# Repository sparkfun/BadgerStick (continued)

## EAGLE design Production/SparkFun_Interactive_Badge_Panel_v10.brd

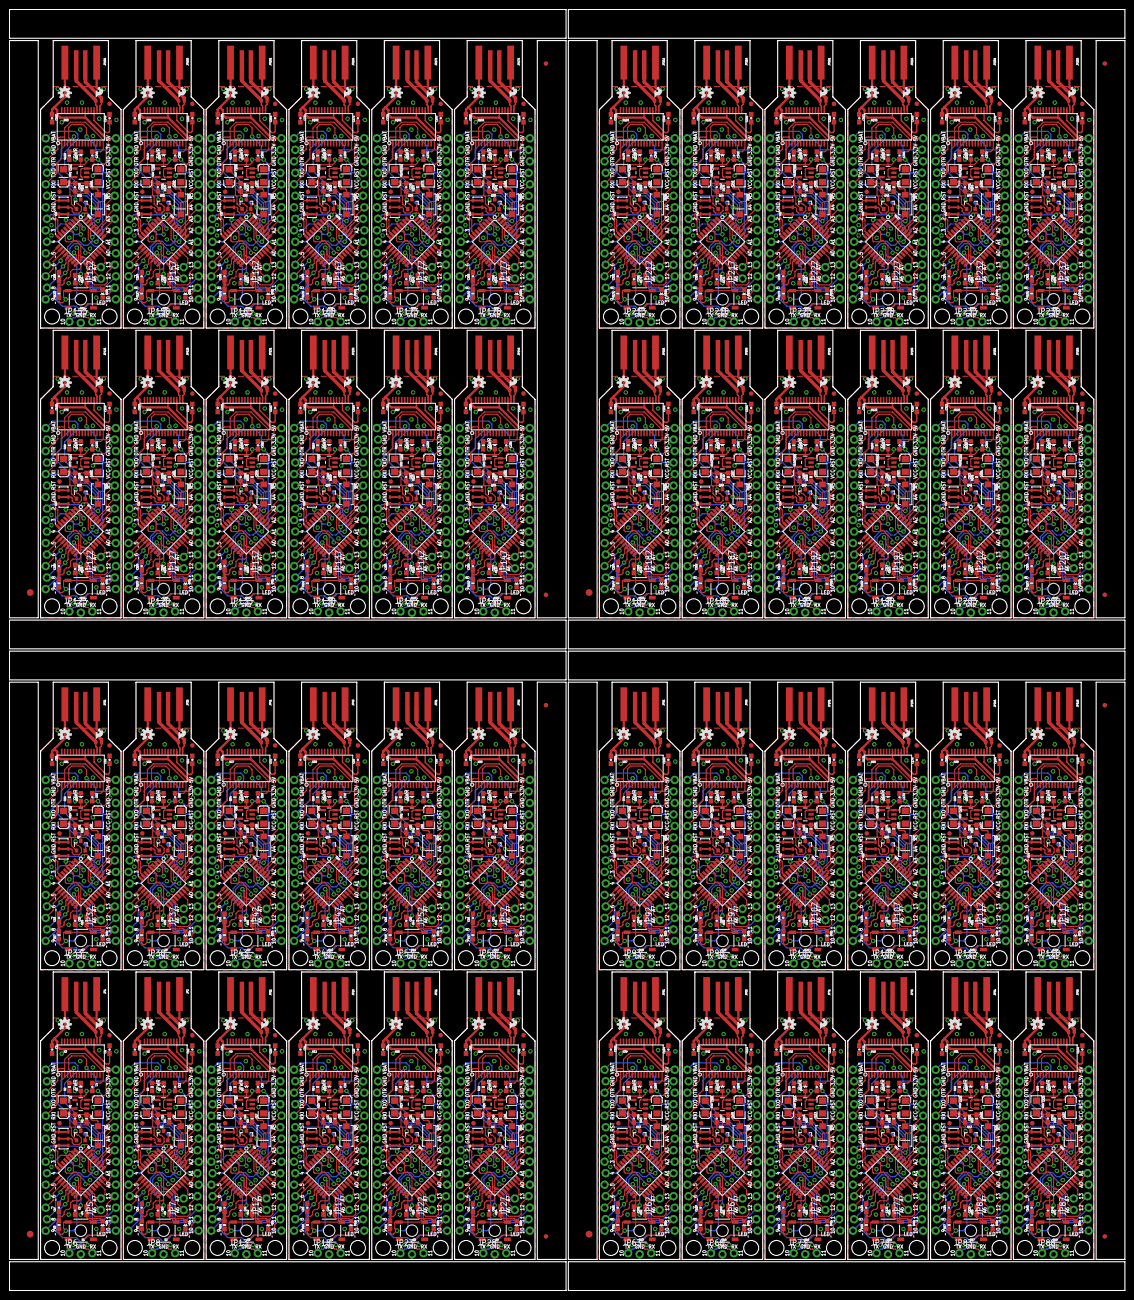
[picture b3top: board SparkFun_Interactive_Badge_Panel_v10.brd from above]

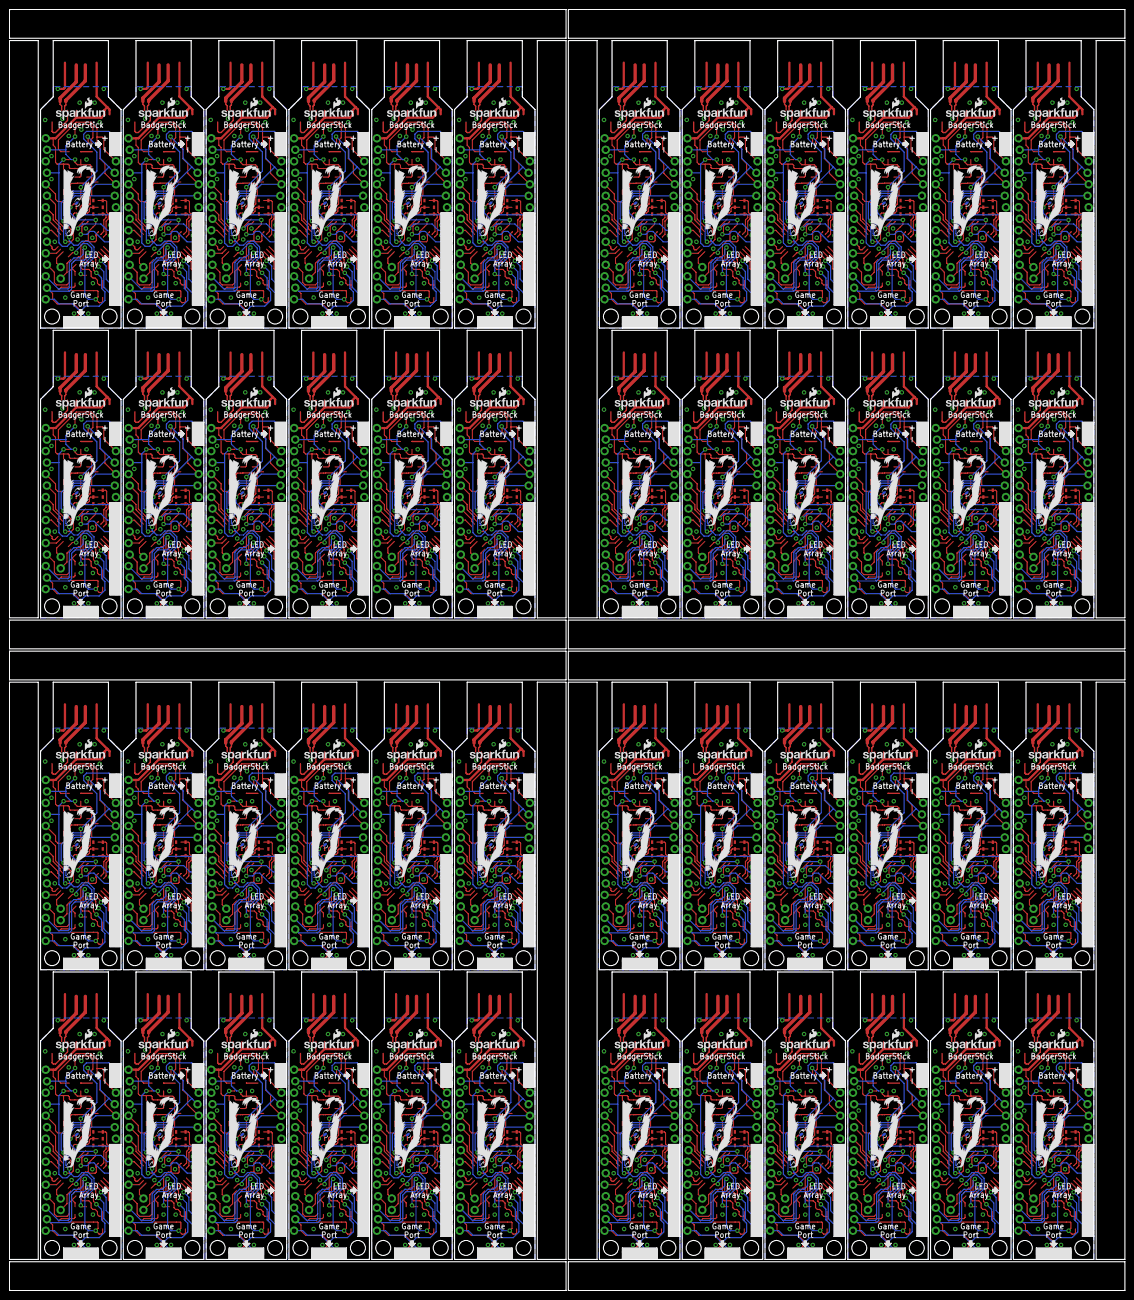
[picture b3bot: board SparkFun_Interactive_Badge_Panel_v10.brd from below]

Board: 2 copper layers, 246.4 x 283.0 mm, 1644 parts (96 on the bottom side), 1776 nets.

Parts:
C1, C2, C9, C10, C17, C18, C25, C26, C33, C34, C41, C42, C49, C50, C57, C58, C65, C66, C73, C74, C81, C82, C89, C90, C97, C98, C105, C106, C113, C114, C121, C122, C129, C130, C137, C138, C145, C146, C153, C154, C161, C162, C169, C170, C177, C178, C185, C186, C193, C194, C201, C202, C209, C210, C217, C218, C225, C226, C233, C234, C241, C242, C249, C250, C257, C258, C265, C266, C273, C274, C281, C282, C289, C290, C297, C298, C305, C306, C313, C314, C321, C322, C329, C330, C337, C338, C345, C346, C353, C354, C361, C362, C369, C370, C377, C378: 10uF; EIA3216
C3, C4, C5, C6, C7, C8, C11, C12, C13, C14, C15, C16, C19, C20, C21, C22, C23, C24, C27, C28, C29, C30, C31, C32, C35, C36, C37, C38, C39, C40, C43, C44, C45, C46, C47, C48, C51, C52, C53, C54, C55, C56, C59, C60, C61, C62, C63, C64, C67, C68, C69, C70, C71, C72, C75, C76, C77, C78, C79, C80, C83, C84, C85, C86, C87, C88, C91, C92, C93, C94, C95, C96, C99, C100, C101, C102, C103, C104, C107, C108, C109, C110, C111, C112, C115, C116, C117, C118, C119, C120, C123, C124, C125, C126, C127, C128, C131, C132, C133, C134, C135, C136, C139, C140, C141, C142, C143, C144, C147, C148, C149, C150, C151, C152, C155, C156, C157, C158, C159, C160, C163, C164, C165, C166, C167, C168, C171, C172, C173, C174, C175, C176, C179, C180, C181, C182, C183, C184, C187, C188, C189, C190, C191, C192, C195, C196, C197, C198, C199, C200, C203, C204, C205, C206, C207, C208, C211, C212, C213, C214, C215, C216, C219, C220, C221, C222, C223, C224, C227, C228, C229, C230, C231, C232, C235, C236, C237, C238, C239, C240, C243, C244, C245, C246, C247, C248, C251, C252, C253, C254, C255, C256, C259, C260, C261, C262, C263, C264, C267, C268, C269, C270, C271, C272, C275, C276, C277, C278, C279, C280, C283, C284, C285, C286, C287, C288, C291, C292, C293, C294, C295, C296, C299, C300, C301, C302, C303, C304, C307, C308, C309, C310, C311, C312, C315, C316, C317, C318, C319, C320, C323, C324, C325, C326, C327, C328, C331, C332, C333, C334, C335, C336, C339, C340, C341, C342, C343, C344, C347, C348, C349, C350, C351, C352, C355, C356, C357, C358, C359, C360, C363, C364, C365, C366, C367, C368, C371, C372, C373, C374, C375, C376, C379, C380, C381, C382, C383, C384: 0.1uF; 0603-CAP
D1, D4, D7, D10, D13, D16, D19, D22, D25, D28, D31, D34, D37, D40, D43, D46, D49, D52, D55, D58, D61, D64, D67, D70, D73, D76, D79, D82, D85, D88, D91, D94, D97, D100, D103, D106, D109, D112, D115, D118, D121, D124, D127, D130, D133, D136, D139, D142: MBRA140; SMA-DIODE
D2, D5, D8, D11, D14, D17, D20, D23, D26, D29, D32, D35, D38, D41, D44, D47, D50, D53, D56, D59, D62, D65, D68, D71, D74, D77, D80, D83, D86, D89, D92, D95, D98, D101, D104, D107, D110, D113, D116, D119, D122, D125, D128, D131, D134, D137, D140, D143: RED; LED-0603
D3, D6, D9, D12, D15, D18, D21, D24, D27, D30, D33, D36, D39, D42, D45, D48, D51, D54, D57, D60, D63, D66, D69, D72, D75, D78, D81, D84, D87, D90, D93, D96, D99, D102, D105, D108, D111, D114, D117, D120, D123, D126, D129, D132, D135, D138, D141, D144: GREEN; LED-0603
E$1, E$6, E$9, E$12: FIDUCIAL-1.5X3
E$2, E$3, E$4, E$5, E$7, E$8, E$10, E$11: FIDUCIAL-1X2
FID1, FID2, FID3, FID4, FID5, FID6, FID7, FID8, FID9, FID10, FID11, FID12, FID13, FID14, FID15, FID16, FID17, FID18, FID19, FID20, FID21, FID22, FID23, FID24, FID25, FID26, FID27, FID28, FID29, FID30, FID31, FID32, FID33, FID34, FID35, FID36, FID37, FID38, FID39, FID40, FID41, FID42, FID43, FID44, FID45, FID46, FID47, FID48, FID49, FID50, FID51, FID52, FID53, FID54, FID55, FID56, FID57, FID58, FID59, FID60, FID61, FID62, FID63, FID64, FID65, FID66, FID67, FID68, FID69, FID70, FID71, FID72, FID73, FID74, FID75, FID76, FID77, FID78, FID79, FID80, FID81, FID82, FID83, FID84, FID85, FID86, FID87, FID88, FID89, FID90, FID91, FID92, FID93, FID94, FID95, FID96: FIDUCIAL1X2; FIDUCIAL-1X2
JP1, JP2, JP11, JP16, JP21, JP26, JP31, JP36, JP41, JP46, JP51, JP56, JP61, JP66, JP71, JP76, JP81, JP86, JP91, JP96, JP101, JP106, JP111, JP116, JP121, JP126, JP131, JP136, JP141, JP146, JP151, JP156, JP161, JP166, JP171, JP176, JP181, JP186, JP191, JP196, JP201, JP206, JP211, JP216, JP221, JP226, JP231, JP236: USBPCB; USB-A-PCB
JP3, JP4, JP9, JP10, JP14, JP15, JP19, JP20, JP24, JP25, JP29, JP30, JP34, JP35, JP39, JP40, JP44, JP45, JP49, JP50, JP54, JP55, JP59, JP60, JP64, JP65, JP69, JP70, JP74, JP75, JP79, JP80, JP84, JP85, JP89, JP90, JP94, JP95, JP99, JP100, JP104, JP105, JP109, JP110, JP114, JP115, JP119, JP120, JP124, JP125, JP129, JP130, JP134, JP135, JP139, JP140, JP144, JP145, JP149, JP150, JP154, JP155, JP159, JP160, JP164, JP165, JP169, JP170, JP174, JP175, JP179, JP180, JP184, JP185, JP189, JP190, JP194, JP195, JP199, JP200, JP204, JP205, JP209, JP210, JP214, JP215, JP219, JP220, JP224, JP225, JP229, JP230, JP234, JP235, JP239, JP240: M15LOCK_NO_SILK; 1X15_LOCK_NO_SILK
JP5, JP7, JP12, JP17, JP22, JP27, JP32, JP37, JP42, JP47, JP52, JP57, JP62, JP67, JP72, JP77, JP82, JP87, JP92, JP97, JP102, JP107, JP112, JP117, JP122, JP127, JP132, JP137, JP142, JP147, JP152, JP157, JP162, JP167, JP172, JP177, JP182, JP187, JP192, JP197, JP202, JP207, JP212, JP217, JP222, JP227, JP232, JP237: M021X02_NO_SILK; 1X02_NO_SILK
JP6, JP8, JP13, JP18, JP23, JP28, JP33, JP38, JP43, JP48, JP53, JP58, JP63, JP68, JP73, JP78, JP83, JP88, JP93, JP98, JP103, JP108, JP113, JP118, JP123, JP128, JP133, JP138, JP143, JP148, JP153, JP158, JP163, JP168, JP173, JP178, JP183, JP188, JP193, JP198, JP203, JP208, JP213, JP218, JP223, JP228, JP233, JP238: M03LOCK Female; 1X03_LOCK_NO_SILK
LOGO1, LOGO3, LOGO5, LOGO7, LOGO9, LOGO11, LOGO13, LOGO15, LOGO17, LOGO19, LOGO21, LOGO23, LOGO25, LOGO27, LOGO29, LOGO31, LOGO33, LOGO35, LOGO37, LOGO39, LOGO41, LOGO43, LOGO45, LOGO47, LOGO49, LOGO51, LOGO53, LOGO55, LOGO57, LOGO59, LOGO61, LOGO63, LOGO65, LOGO67, LOGO69, LOGO71, LOGO73, LOGO75, LOGO77, LOGO79, LOGO81, LOGO83, LOGO85, LOGO87, LOGO89, LOGO91, LOGO93, LOGO95: SFE_LOGO_FLAME.1_INCH; SFE_LOGO_FLAME_.1
LOGO2, LOGO4, LOGO6, LOGO8, LOGO10, LOGO12, LOGO14, LOGO16, LOGO18, LOGO20, LOGO22, LOGO24, LOGO26, LOGO28, LOGO30, LOGO32, LOGO34, LOGO36, LOGO38, LOGO40, LOGO42, LOGO44, LOGO46, LOGO48, LOGO50, LOGO52, LOGO54, LOGO56, LOGO58, LOGO60, LOGO62, LOGO64, LOGO66, LOGO68, LOGO70, LOGO72, LOGO74, LOGO76, LOGO78, LOGO80, LOGO82, LOGO84, LOGO86, LOGO88, LOGO90, LOGO92, LOGO94, LOGO96: OSHW-LOGOS; OSHW-LOGO-S
Q1, Q2, Q3, Q4, Q5, Q6, Q7, Q8, Q9, Q10, Q11, Q12, Q13, Q14, Q15, Q16, Q17, Q18, Q19, Q20, Q21, Q22, Q23, Q24, Q25, Q26, Q27, Q28, Q29, Q30, Q31, Q32, Q33, Q34, Q35, Q36, Q37, Q38, Q39, Q40, Q41, Q42, Q43, Q44, Q45, Q46, Q47, Q48: DMG2307L; SOT23-3
R1, R5, R9, R13, R17, R21, R25, R29, R33, R37, R41, R45, R49, R53, R57, R61, R65, R69, R73, R77, R81, R85, R89, R93, R97, R101, R105, R109, R113, R117, R121, R125, R129, R133, R137, R141, R145, R149, R153, R157, R161, R165, R169, R173, R177, R181, R185, R189: 100k; 0603-RES
R2, R3, R6, R7, R10, R11, R14, R15, R18, R19, R22, R23, R26, R27, R30, R31, R34, R35, R38, R39, R42, R43, R46, R47, R50, R51, R54, R55, R58, R59, R62, R63, R66, R67, R70, R71, R74, R75, R78, R79, R82, R83, R86, R87, R90, R91, R94, R95, R98, R99, R102, R103, R106, R107, R110, R111, R114, R115, R118, R119, R122, R123, R126, R127, R130, R131, R134, R135, R138, R139, R142, R143, R146, R147, R150, R151, R154, R155, R158, R159, R162, R163, R166, R167, R170, R171, R174, R175, R178, R179, R182, R183, R186, R187, R190, R191: 10K; 0603-RES
R4, R8, R12, R16, R20, R24, R28, R32, R36, R40, R44, R48, R52, R56, R60, R64, R68, R72, R76, R80, R84, R88, R92, R96, R100, R104, R108, R112, R116, R120, R124, R128, R132, R136, R140, R144, R148, R152, R156, R160, R164, R168, R172, R176, R180, R184, R188, R192: 330; 0603-RES
S1, S2, S3, S4, S5, S6, S7, S8, S9, S10, S11, S12, S13, S14, S15, S16, S17, S18, S19, S20, S21, S22, S23, S24, S25, S26, S27, S28, S29, S30, S31, S32, S33, S34, S35, S36, S37, S38, S39, S40, S41, S42, S43, S44, S45, S46, S47, S48: SWITCH-MOMENTARY-2SMD-REDUNDANT; TACTILE-SWITCH-SMD
STANDOFF1, STANDOFF2, STANDOFF3, STANDOFF4, STANDOFF5, STANDOFF6, STANDOFF7, STANDOFF8, STANDOFF9, STANDOFF10, STANDOFF11, STANDOFF12, STANDOFF13, STANDOFF14, STANDOFF15, STANDOFF16, STANDOFF17, STANDOFF18, STANDOFF19, STANDOFF20, STANDOFF21, STANDOFF22, STANDOFF23, STANDOFF24, STANDOFF25, STANDOFF26, STANDOFF27, STANDOFF28, STANDOFF29, STANDOFF30, STANDOFF31, STANDOFF32, STANDOFF33, STANDOFF34, STANDOFF35, STANDOFF36, STANDOFF37, STANDOFF38, STANDOFF39, STANDOFF40, STANDOFF41, STANDOFF42, STANDOFF43, STANDOFF44, STANDOFF45, STANDOFF46, STANDOFF47, STANDOFF48, STANDOFF49, STANDOFF50, STANDOFF51, STANDOFF52, STANDOFF53, STANDOFF54, STANDOFF55, STANDOFF56, STANDOFF57, STANDOFF58, STANDOFF59, STANDOFF60, STANDOFF61, STANDOFF62, STANDOFF63, STANDOFF64, STANDOFF65, STANDOFF66, STANDOFF67, STANDOFF68, STANDOFF69, STANDOFF70, STANDOFF71, STANDOFF72, STANDOFF73, STANDOFF74, STANDOFF75, STANDOFF76, STANDOFF77, STANDOFF78, STANDOFF79, STANDOFF80, STANDOFF81, STANDOFF82, STANDOFF83, STANDOFF84, STANDOFF85, STANDOFF86, STANDOFF87, STANDOFF88, STANDOFF89, STANDOFF90, STANDOFF91, STANDOFF92, STANDOFF93, STANDOFF94, STANDOFF95, STANDOFF96: STAND-OFF
U1, U4, U7, U10, U13, U16, U19, U22, U25, U28, U31, U34, U37, U40, U43, U46, U49, U52, U55, U58, U61, U64, U67, U70, U73, U76, U79, U82, U85, U88, U91, U94, U97, U100, U103, U106, U109, U112, U115, U118, U121, U124, U127, U130, U133, U136, U139, U142: MIC5205-3.3V; SOT23-5
U2, U5, U8, U11, U14, U17, U20, U23, U26, U29, U32, U35, U38, U41, U44, U47, U50, U53, U56, U59, U62, U65, U68, U71, U74, U77, U80, U83, U86, U89, U92, U95, U98, U101, U104, U107, U110, U113, U116, U119, U122, U125, U128, U131, U134, U137, U140, U143: ATMEGA328P; TQFP32-08
U3, U6, U9, U12, U15, U18, U21, U24, U27, U30, U33, U36, U39, U42, U45, U48, U51, U54, U57, U60, U63, U66, U69, U72, U75, U78, U81, U84, U87, U90, U93, U96, U99, U102, U105, U108, U111, U114, U117, U120, U123, U126, U129, U132, U135, U138, U141, U144: CY7C65213; SSOP28DB
U$1, U$2, U$5, U$7, U$9, U$11, U$13, U$15, U$17, U$19, U$21, U$23, U$25, U$27, U$29, U$31, U$33, U$35, U$37, U$39, U$41, U$43, U$45, U$47, U$49, U$51, U$53, U$55, U$57, U$59, U$61, U$63, U$65, U$67, U$69, U$71, U$73, U$75, U$77, U$79, U$81, U$83, U$85, U$87, U$89, U$91, U$93, U$95: SFE_LOGO_NAME_FLAME.1_INCH; SFE_LOGO_NAME_FLAME_.1
U$3, U$4, U$6, U$8, U$10, U$12, U$14, U$16, U$18, U$20, U$22, U$24, U$26, U$28, U$30, U$32, U$34, U$36, U$38, U$40, U$42, U$44, U$46, U$48, U$50, U$52, U$54, U$56, U$58, U$60, U$62, U$64, U$66, U$68, U$70, U$72, U$74, U$76, U$78, U$80, U$82, U$84, U$86, U$88, U$90, U$92, U$94, U$96: HALF_BADGER
Y1, Y2, Y3, Y4, Y5, Y6, Y7, Y8, Y9, Y10, Y11, Y12, Y13, Y14, Y15, Y16, Y17, Y18, Y19, Y20, Y21, Y22, Y23, Y24, Y25, Y26, Y27, Y28, Y29, Y30, Y31, Y32, Y33, Y34, Y35, Y36, Y37, Y38, Y39, Y40, Y41, Y42, Y43, Y44, Y45, Y46, Y47, Y48: 4MHz; RESONATOR-SMD_MED

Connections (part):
3.3V: C2.A, C3.1, D1.A, D2.A, JP4.2, Q1.1, R1.2, U1.5, U3.4
3.3V1: C10.A, C11.1, D4.A, D5.A, JP9.2, Q2.1, R5.2, U4.5, U6.4
3.3V2: C18.A, C19.1, D7.A, D8.A, JP14.2, Q3.1, R9.2, U7.5, U9.4
3.3V3: C26.A, C27.1, D10.A, D11.A, JP19.2, Q4.1, R13.2, U10.5, U12.4
3.3V4: C34.A, C35.1, D13.A, D14.A, JP24.2, Q5.1, R17.2, U13.5, U15.4
3.3V5: C42.A, C43.1, D16.A, D17.A, JP29.2, Q6.1, R21.2, U16.5, U18.4
3.3V6: C50.A, C51.1, D19.A, D20.A, JP34.2, Q7.1, R25.2, U19.5, U21.4
3.3V7: C58.A, C59.1, D22.A, D23.A, JP39.2, Q8.1, R29.2, U22.5, U24.4
3.3V8: C66.A, C67.1, D25.A, D26.A, JP44.2, Q9.1, R33.2, U25.5, U27.4
3.3V9: C74.A, C75.1, D28.A, D29.A, JP49.2, Q10.1, R37.2, U28.5, U30.4
3.3V10: C82.A, C83.1, D31.A, D32.A, JP54.2, Q11.1, R41.2, U31.5, U33.4
3.3V11: C90.A, C91.1, D34.A, D35.A, JP59.2, Q12.1, R45.2, U34.5, U36.4
3.3V12: C98.A, C99.1, D37.A, D38.A, JP64.2, Q13.1, R49.2, U37.5, U39.4
3.3V13: C106.A, C107.1, D40.A, D41.A, JP69.2, Q14.1, R53.2, U40.5, U42.4
3.3V14: C114.A, C115.1, D43.A, D44.A, JP74.2, Q15.1, R57.2, U43.5, U45.4
3.3V15: C122.A, C123.1, D46.A, D47.A, JP79.2, Q16.1, R61.2, U46.5, U48.4
3.3V16: C130.A, C131.1, D49.A, D50.A, JP84.2, Q17.1, R65.2, U49.5, U51.4
3.3V17: C138.A, C139.1, D52.A, D53.A, JP89.2, Q18.1, R69.2, U52.5, U54.4
3.3V18: C146.A, C147.1, D55.A, D56.A, JP94.2, Q19.1, R73.2, U55.5, U57.4
3.3V19: C154.A, C155.1, D58.A, D59.A, JP99.2, Q20.1, R77.2, U58.5, U60.4
3.3V20: C162.A, C163.1, D61.A, D62.A, JP104.2, Q21.1, R81.2, U61.5, U63.4
3.3V21: C170.A, C171.1, D64.A, D65.A, JP109.2, Q22.1, R85.2, U64.5, U66.4
3.3V22: C178.A, C179.1, D67.A, D68.A, JP114.2, Q23.1, R89.2, U67.5, U69.4
3.3V23: C186.A, C187.1, D70.A, D71.A, JP119.2, Q24.1, R93.2, U70.5, U72.4
3.3V24: C194.A, C195.1, D73.A, D74.A, JP124.2, Q25.1, R97.2, U73.5, U75.4
3.3V25: C202.A, C203.1, D76.A, D77.A, JP129.2, Q26.1, R101.2, U76.5, U78.4
3.3V26: C210.A, C211.1, D79.A, D80.A, JP134.2, Q27.1, R105.2, U79.5, U81.4
3.3V27: C218.A, C219.1, D82.A, D83.A, JP139.2, Q28.1, R109.2, U82.5, U84.4
3.3V28: C226.A, C227.1, D85.A, D86.A, JP144.2, Q29.1, R113.2, U85.5, U87.4
3.3V29: C234.A, C235.1, D88.A, D89.A, JP149.2, Q30.1, R117.2, U88.5, U90.4
3.3V30: C242.A, C243.1, D91.A, D92.A, JP154.2, Q31.1, R121.2, U91.5, U93.4
3.3V31: C250.A, C251.1, D94.A, D95.A, JP159.2, Q32.1, R125.2, U94.5, U96.4
3.3V32: C258.A, C259.1, D97.A, D98.A, JP164.2, Q33.1, R129.2, U97.5, U99.4
3.3V33: C266.A, C267.1, D100.A, D101.A, JP169.2, Q34.1, R133.2, U100.5, U102.4
3.3V34: C274.A, C275.1, D103.A, D104.A, JP174.2, Q35.1, R137.2, U103.5, U105.4
3.3V35: C282.A, C283.1, D106.A, D107.A, JP179.2, Q36.1, R141.2, U106.5, U108.4
3.3V36: C290.A, C291.1, D109.A, D110.A, JP184.2, Q37.1, R145.2, U109.5, U111.4
3.3V37: C298.A, C299.1, D112.A, D113.A, JP189.2, Q38.1, R149.2, U112.5, U114.4
3.3V38: C306.A, C307.1, D115.A, D116.A, JP194.2, Q39.1, R153.2, U115.5, U117.4
3.3V39: C314.A, C315.1, D118.A, D119.A, JP199.2, Q40.1, R157.2, U118.5, U120.4
3.3V40: C322.A, C323.1, D121.A, D122.A, JP204.2, Q41.1, R161.2, U121.5, U123.4
3.3V41: C330.A, C331.1, D124.A, D125.A, JP209.2, Q42.1, R165.2, U124.5, U126.4
3.3V42: C338.A, C339.1, D127.A, D128.A, JP214.2, Q43.1, R169.2, U127.5, U129.4
3.3V43: C346.A, C347.1, D130.A, D131.A, JP219.2, Q44.1, R173.2, U130.5, U132.4
3.3V44: C354.A, C355.1, D133.A, D134.A, JP224.2, Q45.1, R177.2, U133.5, U135.4
3.3V45: C362.A, C363.1, D136.A, D137.A, JP229.2, Q46.1, R181.2, U136.5, U138.4
3.3V46: C370.A, C371.1, D139.A, D140.A, JP234.2, Q47.1, R185.2, U139.5, U141.4
3.3V47: C378.A, C379.1, D142.A, D143.A, JP239.2, Q48.1, R189.2, U142.5, U144.4
5V: C1.A, C7.1, JP1.5V, JP4.1, U1.1, U1.3, U3.20
5V1: C9.A, C15.1, JP2.5V, JP9.1, U4.1, U4.3, U6.20
5V2: C17.A, C23.1, JP11.5V, JP14.1, U7.1, U7.3, U9.20
5V3: C25.A, C31.1, JP16.5V, JP19.1, U10.1, U10.3, U12.20
5V4: C33.A, C39.1, JP21.5V, JP24.1, U13.1, U13.3, U15.20
5V5: C41.A, C47.1, JP26.5V, JP29.1, U16.1, U16.3, U18.20
5V6: C49.A, C55.1, JP31.5V, JP34.1, U19.1, U19.3, U21.20
5V7: C57.A, C63.1, JP36.5V, JP39.1, U22.1, U22.3, U24.20
5V8: C65.A, C71.1, JP41.5V, JP44.1, U25.1, U25.3, U27.20
5V9: C73.A, C79.1, JP46.5V, JP49.1, U28.1, U28.3, U30.20
5V10: C81.A, C87.1, JP51.5V, JP54.1, U31.1, U31.3, U33.20
5V11: C89.A, C95.1, JP56.5V, JP59.1, U34.1, U34.3, U36.20
5V12: C97.A, C103.1, JP61.5V, JP64.1, U37.1, U37.3, U39.20
5V13: C105.A, C111.1, JP66.5V, JP69.1, U40.1, U40.3, U42.20
5V14: C113.A, C119.1, JP71.5V, JP74.1, U43.1, U43.3, U45.20
5V15: C121.A, C127.1, JP76.5V, JP79.1, U46.1, U46.3, U48.20
5V16: C129.A, C135.1, JP81.5V, JP84.1, U49.1, U49.3, U51.20
5V17: C137.A, C143.1, JP86.5V, JP89.1, U52.1, U52.3, U54.20
5V18: C145.A, C151.1, JP91.5V, JP94.1, U55.1, U55.3, U57.20
5V19: C153.A, C159.1, JP96.5V, JP99.1, U58.1, U58.3, U60.20
5V20: C161.A, C167.1, JP101.5V, JP104.1, U61.1, U61.3, U63.20
5V21: C169.A, C175.1, JP106.5V, JP109.1, U64.1, U64.3, U66.20
5V22: C177.A, C183.1, JP111.5V, JP114.1, U67.1, U67.3, U69.20
5V23: C185.A, C191.1, JP116.5V, JP119.1, U70.1, U70.3, U72.20
5V24: C193.A, C199.1, JP121.5V, JP124.1, U73.1, U73.3, U75.20
5V25: C201.A, C207.1, JP126.5V, JP129.1, U76.1, U76.3, U78.20
5V26: C209.A, C215.1, JP131.5V, JP134.1, U79.1, U79.3, U81.20
5V27: C217.A, C223.1, JP136.5V, JP139.1, U82.1, U82.3, U84.20
5V28: C225.A, C231.1, JP141.5V, JP144.1, U85.1, U85.3, U87.20
5V29: C233.A, C239.1, JP146.5V, JP149.1, U88.1, U88.3, U90.20
5V30: C241.A, C247.1, JP151.5V, JP154.1, U91.1, U91.3, U93.20
5V31: C249.A, C255.1, JP156.5V, JP159.1, U94.1, U94.3, U96.20
5V32: C257.A, C263.1, JP161.5V, JP164.1, U97.1, U97.3, U99.20
5V33: C265.A, C271.1, JP166.5V, JP169.1, U100.1, U100.3, U102.20
5V34: C273.A, C279.1, JP171.5V, JP174.1, U103.1, U103.3, U105.20
5V35: C281.A, C287.1, JP176.5V, JP179.1, U106.1, U106.3, U108.20
5V36: C289.A, C295.1, JP181.5V, JP184.1, U109.1, U109.3, U111.20
5V37: C297.A, C303.1, JP186.5V, JP189.1, U112.1, U112.3, U114.20
5V38: C305.A, C311.1, JP191.5V, JP194.1, U115.1, U115.3, U117.20
5V39: C313.A, C319.1, JP196.5V, JP199.1, U118.1, U118.3, U120.20
5V40: C321.A, C327.1, JP201.5V, JP204.1, U121.1, U121.3, U123.20
5V41: C329.A, C335.1, JP206.5V, JP209.1, U124.1, U124.3, U126.20
5V42: C337.A, C343.1, JP211.5V, JP214.1, U127.1, U127.3, U129.20
5V43: C345.A, C351.1, JP216.5V, JP219.1, U130.1, U130.3, U132.20
5V44: C353.A, C359.1, JP221.5V, JP224.1, U133.1, U133.3, U135.20
5V45: C361.A, C367.1, JP226.5V, JP229.1, U136.1, U136.3, U138.20
5V46: C369.A, C375.1, JP231.5V, JP234.1, U139.1, U139.3, U141.20
5V47: C377.A, C383.1, JP236.5V, JP239.1, U142.1, U142.3, U144.20
A0: JP4.11, U2.23
A1: JP4.10, U2.24
A2: JP4.9, U2.25
A3: JP4.8, U2.26
A4: JP4.7, U2.27
A5: JP4.6, U2.28
A6: JP5.1, U2.19
A7: JP5.2, U2.22
A8: JP9.11, U5.23
A9: JP9.10, U5.24
A10: JP9.9, U5.25
A11: JP9.8, U5.26
A12: JP9.7, U5.27
A13: JP9.6, U5.28
A14: JP7.1, U5.19
A15: JP7.2, U5.22
A16: JP14.11, U8.23
A17: JP14.10, U8.24
A18: JP14.9, U8.25
A19: JP14.8, U8.26
A20: JP14.7, U8.27
A21: JP14.6, U8.28
A22: JP12.1, U8.19
A23: JP12.2, U8.22
A24: JP19.11, U11.23
A25: JP19.10, U11.24
A26: JP19.9, U11.25
A27: JP19.8, U11.26
A28: JP19.7, U11.27
A29: JP19.6, U11.28
A30: JP17.1, U11.19
A31: JP17.2, U11.22
A32: JP24.11, U14.23
A33: JP24.10, U14.24
A34: JP24.9, U14.25
A35: JP24.8, U14.26
A36: JP24.7, U14.27
A37: JP24.6, U14.28
A38: JP22.1, U14.19
A39: JP22.2, U14.22
A40: JP29.11, U17.23
A41: JP29.10, U17.24
A42: JP29.9, U17.25
A43: JP29.8, U17.26
A44: JP29.7, U17.27
A45: JP29.6, U17.28
A46: JP27.1, U17.19
A47: JP27.2, U17.22
A48: JP34.11, U20.23
A49: JP34.10, U20.24
A50: JP34.9, U20.25
A51: JP34.8, U20.26
A52: JP34.7, U20.27
A53: JP34.6, U20.28
A54: JP32.1, U20.19
A55: JP32.2, U20.22
A56: JP39.11, U23.23
A57: JP39.10, U23.24
A58: JP39.9, U23.25
A59: JP39.8, U23.26
A60: JP39.7, U23.27
A61: JP39.6, U23.28
A62: JP37.1, U23.19
A63: JP37.2, U23.22
A64: JP44.11, U26.23
A65: JP44.10, U26.24
A66: JP44.9, U26.25
A67: JP44.8, U26.26
A68: JP44.7, U26.27
A69: JP44.6, U26.28
A70: JP42.1, U26.19
A71: JP42.2, U26.22
A72: JP49.11, U29.23
A73: JP49.10, U29.24
A74: JP49.9, U29.25
A75: JP49.8, U29.26
A76: JP49.7, U29.27
A77: JP49.6, U29.28
A78: JP47.1, U29.19
A79: JP47.2, U29.22
A80: JP54.11, U32.23
A81: JP54.10, U32.24
A82: JP54.9, U32.25
A83: JP54.8, U32.26
A84: JP54.7, U32.27
A85: JP54.6, U32.28
A86: JP52.1, U32.19
A87: JP52.2, U32.22
A88: JP59.11, U35.23
A89: JP59.10, U35.24
A90: JP59.9, U35.25
A91: JP59.8, U35.26
A92: JP59.7, U35.27
A93: JP59.6, U35.28
A94: JP57.1, U35.19
A95: JP57.2, U35.22
A96: JP64.11, U38.23
A97: JP64.10, U38.24
A98: JP64.9, U38.25
A99: JP64.8, U38.26
A100: JP64.7, U38.27
A101: JP64.6, U38.28
A102: JP62.1, U38.19
A103: JP62.2, U38.22
A104: JP69.11, U41.23
A105: JP69.10, U41.24
A106: JP69.9, U41.25
A107: JP69.8, U41.26
A108: JP69.7, U41.27
A109: JP69.6, U41.28
A110: JP67.1, U41.19
A111: JP67.2, U41.22
A112: JP74.11, U44.23
A113: JP74.10, U44.24
A114: JP74.9, U44.25
A115: JP74.8, U44.26
A116: JP74.7, U44.27
A117: JP74.6, U44.28
A118: JP72.1, U44.19
A119: JP72.2, U44.22
A120: JP79.11, U47.23
A121: JP79.10, U47.24
A122: JP79.9, U47.25
A123: JP79.8, U47.26
A124: JP79.7, U47.27
A125: JP79.6, U47.28
A126: JP77.1, U47.19
A127: JP77.2, U47.22
A128: JP84.11, U50.23
A129: JP84.10, U50.24
A130: JP84.9, U50.25
A131: JP84.8, U50.26
A132: JP84.7, U50.27
A133: JP84.6, U50.28
A134: JP82.1, U50.19
A135: JP82.2, U50.22
A136: JP89.11, U53.23
A137: JP89.10, U53.24
A138: JP89.9, U53.25
A139: JP89.8, U53.26
A140: JP89.7, U53.27
A141: JP89.6, U53.28
A142: JP87.1, U53.19
A143: JP87.2, U53.22
A144: JP94.11, U56.23
A145: JP94.10, U56.24
A146: JP94.9, U56.25
A147: JP94.8, U56.26
A148: JP94.7, U56.27
A149: JP94.6, U56.28
A150: JP92.1, U56.19
A151: JP92.2, U56.22
A152: JP99.11, U59.23
A153: JP99.10, U59.24
A154: JP99.9, U59.25
A155: JP99.8, U59.26
A156: JP99.7, U59.27
A157: JP99.6, U59.28
A158: JP97.1, U59.19
A159: JP97.2, U59.22
A160: JP104.11, U62.23
A161: JP104.10, U62.24
A162: JP104.9, U62.25
A163: JP104.8, U62.26
A164: JP104.7, U62.27
A165: JP104.6, U62.28
A166: JP102.1, U62.19
A167: JP102.2, U62.22
A168: JP109.11, U65.23
A169: JP109.10, U65.24
A170: JP109.9, U65.25
A171: JP109.8, U65.26
A172: JP109.7, U65.27
A173: JP109.6, U65.28
A174: JP107.1, U65.19
A175: JP107.2, U65.22
A176: JP114.11, U68.23
A177: JP114.10, U68.24
A178: JP114.9, U68.25
A179: JP114.8, U68.26
A180: JP114.7, U68.27
A181: JP114.6, U68.28
A182: JP112.1, U68.19
A183: JP112.2, U68.22
A184: JP119.11, U71.23
A185: JP119.10, U71.24
A186: JP119.9, U71.25
A187: JP119.8, U71.26
A188: JP119.7, U71.27
A189: JP119.6, U71.28
A190: JP117.1, U71.19
A191: JP117.2, U71.22
A192: JP124.11, U74.23
A193: JP124.10, U74.24
A194: JP124.9, U74.25
A195: JP124.8, U74.26
A196: JP124.7, U74.27
A197: JP124.6, U74.28
A198: JP122.1, U74.19
A199: JP122.2, U74.22
A200: JP129.11, U77.23
A201: JP129.10, U77.24
A202: JP129.9, U77.25
A203: JP129.8, U77.26
A204: JP129.7, U77.27
A205: JP129.6, U77.28
A206: JP127.1, U77.19
A207: JP127.2, U77.22
A208: JP134.11, U80.23
A209: JP134.10, U80.24
A210: JP134.9, U80.25
A211: JP134.8, U80.26
A212: JP134.7, U80.27
A213: JP134.6, U80.28
A214: JP132.1, U80.19
A215: JP132.2, U80.22
A216: JP139.11, U83.23
A217: JP139.10, U83.24
A218: JP139.9, U83.25
A219: JP139.8, U83.26
A220: JP139.7, U83.27
A221: JP139.6, U83.28
A222: JP137.1, U83.19
A223: JP137.2, U83.22
A224: JP144.11, U86.23
A225: JP144.10, U86.24
A226: JP144.9, U86.25
A227: JP144.8, U86.26
A228: JP144.7, U86.27
A229: JP144.6, U86.28
A230: JP142.1, U86.19
A231: JP142.2, U86.22
A232: JP149.11, U89.23
A233: JP149.10, U89.24
A234: JP149.9, U89.25
A235: JP149.8, U89.26
A236: JP149.7, U89.27
A237: JP149.6, U89.28
A238: JP147.1, U89.19
A239: JP147.2, U89.22
A240: JP154.11, U92.23
A241: JP154.10, U92.24
A242: JP154.9, U92.25
A243: JP154.8, U92.26
A244: JP154.7, U92.27
A245: JP154.6, U92.28
A246: JP152.1, U92.19
A247: JP152.2, U92.22
A248: JP159.11, U95.23
A249: JP159.10, U95.24
A250: JP159.9, U95.25
A251: JP159.8, U95.26
A252: JP159.7, U95.27
A253: JP159.6, U95.28
A254: JP157.1, U95.19
A255: JP157.2, U95.22
A256: JP164.11, U98.23
A257: JP164.10, U98.24
A258: JP164.9, U98.25
A259: JP164.8, U98.26
A260: JP164.7, U98.27
A261: JP164.6, U98.28
A262: JP162.1, U98.19
A263: JP162.2, U98.22
A264: JP169.11, U101.23
A265: JP169.10, U101.24
A266: JP169.9, U101.25
A267: JP169.8, U101.26
A268: JP169.7, U101.27
A269: JP169.6, U101.28
A270: JP167.1, U101.19
A271: JP167.2, U101.22
A272: JP174.11, U104.23
A273: JP174.10, U104.24
A274: JP174.9, U104.25
A275: JP174.8, U104.26
A276: JP174.7, U104.27
A277: JP174.6, U104.28
A278: JP172.1, U104.19
A279: JP172.2, U104.22
A280: JP179.11, U107.23
A281: JP179.10, U107.24
A282: JP179.9, U107.25
A283: JP179.8, U107.26
A284: JP179.7, U107.27
A285: JP179.6, U107.28
A286: JP177.1, U107.19
A287: JP177.2, U107.22
A288: JP184.11, U110.23
A289: JP184.10, U110.24
A290: JP184.9, U110.25
A291: JP184.8, U110.26
A292: JP184.7, U110.27
A293: JP184.6, U110.28
A294: JP182.1, U110.19
A295: JP182.2, U110.22
A296: JP189.11, U113.23
A297: JP189.10, U113.24
A298: JP189.9, U113.25
A299: JP189.8, U113.26
A300: JP189.7, U113.27
A301: JP189.6, U113.28
A302: JP187.1, U113.19
A303: JP187.2, U113.22
A304: JP194.11, U116.23
A305: JP194.10, U116.24
A306: JP194.9, U116.25
A307: JP194.8, U116.26
A308: JP194.7, U116.27
A309: JP194.6, U116.28
A310: JP192.1, U116.19
A311: JP192.2, U116.22
A312: JP199.11, U119.23
A313: JP199.10, U119.24
A314: JP199.9, U119.25
A315: JP199.8, U119.26
A316: JP199.7, U119.27
A317: JP199.6, U119.28
A318: JP197.1, U119.19
A319: JP197.2, U119.22
A320: JP204.11, U122.23
A321: JP204.10, U122.24
A322: JP204.9, U122.25
A323: JP204.8, U122.26
A324: JP204.7, U122.27
A325: JP204.6, U122.28
A326: JP202.1, U122.19
A327: JP202.2, U122.22
A328: JP209.11, U125.23
A329: JP209.10, U125.24
A330: JP209.9, U125.25
A331: JP209.8, U125.26
A332: JP209.7, U125.27
A333: JP209.6, U125.28
A334: JP207.1, U125.19
A335: JP207.2, U125.22
A336: JP214.11, U128.23
A337: JP214.10, U128.24
A338: JP214.9, U128.25
A339: JP214.8, U128.26
A340: JP214.7, U128.27
A341: JP214.6, U128.28
A342: JP212.1, U128.19
A343: JP212.2, U128.22
A344: JP219.11, U131.23
A345: JP219.10, U131.24
A346: JP219.9, U131.25
A347: JP219.8, U131.26
A348: JP219.7, U131.27
A349: JP219.6, U131.28
A350: JP217.1, U131.19
A351: JP217.2, U131.22
A352: JP224.11, U134.23
A353: JP224.10, U134.24
A354: JP224.9, U134.25
A355: JP224.8, U134.26
A356: JP224.7, U134.27
A357: JP224.6, U134.28
A358: JP222.1, U134.19
A359: JP222.2, U134.22
A360: JP229.11, U137.23
A361: JP229.10, U137.24
A362: JP229.9, U137.25
A363: JP229.8, U137.26
A364: JP229.7, U137.27
A365: JP229.6, U137.28
A366: JP227.1, U137.19
A367: JP227.2, U137.22
A368: JP234.11, U140.23
A369: JP234.10, U140.24
A370: JP234.9, U140.25
A371: JP234.8, U140.26
A372: JP234.7, U140.27
A373: JP234.6, U140.28
A374: JP232.1, U140.19
A375: JP232.2, U140.22
A376: JP239.11, U143.23
A377: JP239.10, U143.24
A378: JP239.9, U143.25
A379: JP239.8, U143.26
A380: JP239.7, U143.27
A381: JP239.6, U143.28
A382: JP237.1, U143.19
A383: JP237.2, U143.22
AREF: C5.1, U2.20
AREF1: C13.1, U5.20
AREF2: C21.1, U8.20
AREF3: C29.1, U11.20
AREF4: C37.1, U14.20
AREF5: C45.1, U17.20
AREF6: C53.1, U20.20
AREF7: C61.1, U23.20
AREF8: C69.1, U26.20
AREF9: C77.1, U29.20
AREF10: C85.1, U32.20
AREF11: C93.1, U35.20
AREF12: C101.1, U38.20
AREF13: C109.1, U41.20
AREF14: C117.1, U44.20
AREF15: C125.1, U47.20
AREF16: C133.1, U50.20
AREF17: C141.1, U53.20
AREF18: C149.1, U56.20
AREF19: C157.1, U59.20
AREF20: C165.1, U62.20
AREF21: C173.1, U65.20
AREF22: C181.1, U68.20
AREF23: C189.1, U71.20
AREF24: C197.1, U74.20
AREF25: C205.1, U77.20
AREF26: C213.1, U80.20
AREF27: C221.1, U83.20
AREF28: C229.1, U86.20
AREF29: C237.1, U89.20
AREF30: C245.1, U92.20
AREF31: C253.1, U95.20
AREF32: C261.1, U98.20
AREF33: C269.1, U101.20
AREF34: C277.1, U104.20
AREF35: C285.1, U107.20
AREF36: C293.1, U110.20
AREF37: C301.1, U113.20
AREF38: C309.1, U116.20
AREF39: C317.1, U119.20
AREF40: C325.1, U122.20
AREF41: C333.1, U125.20
AREF42: C341.1, U128.20
AREF43: C349.1, U131.20
AREF44: C357.1, U134.20
AREF45: C365.1, U137.20
AREF46: C373.1, U140.20
AREF47: C381.1, U143.20
D1: JP10.8, U5.32
D2: JP3.8, U2.32
D3: JP3.7, U2.1
D4: JP3.6, U2.2
D5: JP3.5, U2.9
D6: JP3.4, U2.10
D7: JP3.3, U2.11
D8: JP3.2, U2.12
D9: JP3.1, U2.13
D10: JP4.15, JP6.1, U2.14
D11: JP10.7, U5.1
D12: JP10.6, U5.2
D13: JP10.5, U5.9
D14: JP10.4, U5.10
D15: JP10.3, U5.11
D16: JP10.2, U5.12
D17: JP10.1, U5.13
D18: JP8.1, JP9.15, U5.14
D19: JP15.8, U8.32
D20: JP15.7, U8.1
D21: JP15.6, U8.2
D22: JP15.5, U8.9
D23: JP15.4, U8.10
D24: JP15.3, U8.11
D25: JP15.2, U8.12
D26: JP15.1, U8.13
D27: JP13.1, JP14.15, U8.14
D28: JP20.8, U11.32
D29: JP20.7, U11.1
D30: JP20.6, U11.2
D31: JP20.5, U11.9
D32: JP20.4, U11.10
D33: JP20.3, U11.11
D34: JP20.2, U11.12
D35: JP20.1, U11.13
D36: JP18.1, JP19.15, U11.14
D37: JP25.8, U14.32
D38: JP25.7, U14.1
D39: JP25.6, U14.2
D40: JP25.5, U14.9
D41: JP25.4, U14.10
D42: JP25.3, U14.11
D43: JP25.2, U14.12
D44: JP25.1, U14.13
D45: JP23.1, JP24.15, U14.14
D46: JP30.8, U17.32
D47: JP30.7, U17.1
D48: JP30.6, U17.2
D49: JP30.5, U17.9
D50: JP30.4, U17.10
D51: JP30.3, U17.11
D52: JP30.2, U17.12
D53: JP30.1, U17.13
D54: JP28.1, JP29.15, U17.14
D55: JP35.8, U20.32
D56: JP35.7, U20.1
D57: JP35.6, U20.2
D58: JP35.5, U20.9
D59: JP35.4, U20.10
D60: JP35.3, U20.11
D61: JP35.2, U20.12
D62: JP35.1, U20.13
D63: JP33.1, JP34.15, U20.14
D64: JP40.8, U23.32
D65: JP40.7, U23.1
D66: JP40.6, U23.2
D67: JP40.5, U23.9
D68: JP40.4, U23.10
D69: JP40.3, U23.11
D70: JP40.2, U23.12
D71: JP40.1, U23.13
D72: JP38.1, JP39.15, U23.14
D73: JP45.8, U26.32
D74: JP45.7, U26.1
D75: JP45.6, U26.2
D76: JP45.5, U26.9
D77: JP45.4, U26.10
D78: JP45.3, U26.11
D79: JP45.2, U26.12
D80: JP45.1, U26.13
D81: JP43.1, JP44.15, U26.14
D82: JP50.8, U29.32
D83: JP50.7, U29.1
D84: JP50.6, U29.2
D85: JP50.5, U29.9
D86: JP50.4, U29.10
D87: JP50.3, U29.11
D88: JP50.2, U29.12
D89: JP50.1, U29.13
D90: JP48.1, JP49.15, U29.14
D91: JP55.8, U32.32
D92: JP55.7, U32.1
D93: JP55.6, U32.2
D94: JP55.5, U32.9
D95: JP55.4, U32.10
D96: JP55.3, U32.11
D97: JP55.2, U32.12
D98: JP55.1, U32.13
D99: JP53.1, JP54.15, U32.14
D100: JP60.8, U35.32
D101: JP60.7, U35.1
D102: JP60.6, U35.2
D103: JP60.5, U35.9
D104: JP60.4, U35.10
D105: JP60.3, U35.11
D106: JP60.2, U35.12
D107: JP60.1, U35.13
D108: JP58.1, JP59.15, U35.14
D109: JP65.8, U38.32
D110: JP65.7, U38.1
D111: JP65.6, U38.2
D112: JP65.5, U38.9
D113: JP65.4, U38.10
D114: JP65.3, U38.11
D115: JP65.2, U38.12
D116: JP65.1, U38.13
D117: JP63.1, JP64.15, U38.14
D118: JP70.8, U41.32
D119: JP70.7, U41.1
D120: JP70.6, U41.2
D121: JP70.5, U41.9
D122: JP70.4, U41.10
D123: JP70.3, U41.11
D124: JP70.2, U41.12
D125: JP70.1, U41.13
D126: JP68.1, JP69.15, U41.14
D127: JP75.8, U44.32
D128: JP75.7, U44.1
D129: JP75.6, U44.2
D130: JP75.5, U44.9
D131: JP75.4, U44.10
D132: JP75.3, U44.11
D133: JP75.2, U44.12
D134: JP75.1, U44.13
D135: JP73.1, JP74.15, U44.14
D136: JP80.8, U47.32
D137: JP80.7, U47.1
D138: JP80.6, U47.2
D139: JP80.5, U47.9
D140: JP80.4, U47.10
D141: JP80.3, U47.11
D142: JP80.2, U47.12
D143: JP80.1, U47.13
D144: JP78.1, JP79.15, U47.14
D145: JP85.8, U50.32
D146: JP85.7, U50.1
D147: JP85.6, U50.2
D148: JP85.5, U50.9
D149: JP85.4, U50.10
D150: JP85.3, U50.11
D151: JP85.2, U50.12
D152: JP85.1, U50.13
D153: JP83.1, JP84.15, U50.14
D154: JP90.8, U53.32
D155: JP90.7, U53.1
D156: JP90.6, U53.2
D157: JP90.5, U53.9
D158: JP90.4, U53.10
D159: JP90.3, U53.11
D160: JP90.2, U53.12
D161: JP90.1, U53.13
D162: JP88.1, JP89.15, U53.14
D163: JP95.8, U56.32
D164: JP95.7, U56.1
D165: JP95.6, U56.2
D166: JP95.5, U56.9
D167: JP95.4, U56.10
D168: JP95.3, U56.11
D169: JP95.2, U56.12
D170: JP95.1, U56.13
D171: JP93.1, JP94.15, U56.14
D172: JP100.8, U59.32
D173: JP100.7, U59.1
D174: JP100.6, U59.2
D175: JP100.5, U59.9
D176: JP100.4, U59.10
D177: JP100.3, U59.11
D178: JP100.2, U59.12
D179: JP100.1, U59.13
D180: JP98.1, JP99.15, U59.14
D181: JP105.8, U62.32
D182: JP105.7, U62.1
D183: JP105.6, U62.2
D184: JP105.5, U62.9
D185: JP105.4, U62.10
D186: JP105.3, U62.11
D187: JP105.2, U62.12
D188: JP105.1, U62.13
D189: JP103.1, JP104.15, U62.14
D190: JP110.8, U65.32
D191: JP110.7, U65.1
D192: JP110.6, U65.2
D193: JP110.5, U65.9
D194: JP110.4, U65.10
D195: JP110.3, U65.11
D196: JP110.2, U65.12
D197: JP110.1, U65.13
D198: JP108.1, JP109.15, U65.14
D199: JP115.8, U68.32
D200: JP115.7, U68.1
D201: JP115.6, U68.2
D202: JP115.5, U68.9
D203: JP115.4, U68.10
D204: JP115.3, U68.11
D205: JP115.2, U68.12
D206: JP115.1, U68.13
D207: JP113.1, JP114.15, U68.14
D208: JP120.8, U71.32
D209: JP120.7, U71.1
D210: JP120.6, U71.2
D211: JP120.5, U71.9
D212: JP120.4, U71.10
D213: JP120.3, U71.11
D214: JP120.2, U71.12
D215: JP120.1, U71.13
D216: JP118.1, JP119.15, U71.14
D217: JP125.8, U74.32
D218: JP125.7, U74.1
D219: JP125.6, U74.2
D220: JP125.5, U74.9
D221: JP125.4, U74.10
D222: JP125.3, U74.11
D223: JP125.2, U74.12
D224: JP125.1, U74.13
D225: JP123.1, JP124.15, U74.14
D226: JP130.8, U77.32
D227: JP130.7, U77.1
D228: JP130.6, U77.2
D229: JP130.5, U77.9
D230: JP130.4, U77.10
D231: JP130.3, U77.11
D232: JP130.2, U77.12
D233: JP130.1, U77.13
D234: JP128.1, JP129.15, U77.14
D235: JP135.8, U80.32
D236: JP135.7, U80.1
D237: JP135.6, U80.2
D238: JP135.5, U80.9
D239: JP135.4, U80.10
D240: JP135.3, U80.11
D241: JP135.2, U80.12
D242: JP135.1, U80.13
D243: JP133.1, JP134.15, U80.14
D244: JP140.8, U83.32
D245: JP140.7, U83.1
D246: JP140.6, U83.2
D247: JP140.5, U83.9
D248: JP140.4, U83.10
D249: JP140.3, U83.11
D250: JP140.2, U83.12
D251: JP140.1, U83.13
D252: JP138.1, JP139.15, U83.14
D253: JP145.8, U86.32
D254: JP145.7, U86.1
D255: JP145.6, U86.2
D256: JP145.5, U86.9
D257: JP145.4, U86.10
D258: JP145.3, U86.11
D259: JP145.2, U86.12
D260: JP145.1, U86.13
D261: JP143.1, JP144.15, U86.14
D262: JP150.8, U89.32
D263: JP150.7, U89.1
D264: JP150.6, U89.2
D265: JP150.5, U89.9
D266: JP150.4, U89.10
D267: JP150.3, U89.11
D268: JP150.2, U89.12
D269: JP150.1, U89.13
D270: JP148.1, JP149.15, U89.14
D271: JP155.8, U92.32
D272: JP155.7, U92.1
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
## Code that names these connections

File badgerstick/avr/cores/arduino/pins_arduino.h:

/*
  pins_arduino.h - Pin definition functions for Arduino
  Part of Arduino - http://www.arduino.cc/

  Copyright (c) 2007 David A. Mellis
  Modified by Shawn Hymel @ SparkFun Electronics to support the BadgerStick

  This library is free software; you can redistribute it and/or
  modify it under the terms of the GNU Lesser General Public
  License as published by the Free Software Foundation; either
  version 2.1 of the License, or (at your option) any later version.

  This library is distributed in the hope that it will be useful,
  but WITHOUT ANY WARRANTY; without even the implied warranty of
  MERCHANTABILITY or FITNESS FOR A PARTICULAR PURPOSE.  See the GNU
  Lesser General Public License for more details.

  You should have received a copy of the GNU Lesser General
  Public License along with this library; if not, write to the
  Free Software Foundation, Inc., 59 Temple Place, Suite 330,
  Boston, MA  02111-1307  USA

  $Id: wiring.h 249 2007-02-03 16:52:51Z mellis $
*/

#ifndef Pins_Arduino_h
#define Pins_Arduino_h

#include <avr/pgmspace.h>

#define NUM_DIGITAL_PINS            20
#define NUM_ANALOG_INPUTS           8
#define analogInputToDigitalPin(p)  ((p < 6) ? (p) + 14 : -1)

#if defined(__AVR_ATmega8__)
#define digitalPinHasPWM(p)         ((p) == 9 || (p) == 10 || (p) == 11)
#else
#define digitalPinHasPWM(p)         ((p) == 3 || (p) == 5 || (p) == 6 || (p) == 9 || (p) == 10 || (p) == 11)
#endif

static const uint8_t SS   = 10;
static const uint8_t MOSI = 11;
static const uint8_t MISO = 12;
static const uint8_t SCK  = 13;

static const uint8_t SDA = 18;
static const uint8_t SCL = 19;
#define LED_BUILTIN 13

static const uint8_t A0 = 14;
static const uint8_t A1 = 15;
static const uint8_t A2 = 16;
static const uint8_t A3 = 17;
static const uint8_t A4 = 18;
static const uint8_t A5 = 19;
static const uint8_t A6 = 20;
static const uint8_t A7 = 21;

#define digitalPinToPCICR(p)    (((p) >= 0 && (p) <= 21) ? (&PCICR) : ((uint8_t *)0))
#define digitalPinToPCICRbit(p) (((p) <= 7) ? 2 : (((p) <= 13) ? 0 : 1))
#define digitalPinToPCMSK(p)    (((p) <= 7) ? (&PCMSK2) : (((p) <= 13) ? (&PCMSK0) : (((p) <= 21) ? (&PCMSK1) : ((uint8_t *)0))))
#define digitalPinToPCMSKbit(p) (((p) <= 7) ? (p) : (((p) <= 13) ? ((p) - 8) : ((p) - 14)))

#define digitalPinToInterrupt(p)  ((p) == 2 ? 0 : ((p) == 3 ? 1 : NOT_AN_INTERRUPT))

#ifdef ARDUINO_MAIN

// On the Arduino board, digital pins are also used
// for the analog output (software PWM).  Analog input
// pins are a separate set.

// ATMEL ATMEGA8 & 168 / ARDUINO
//
//                  +-\/-+
//            PC6  1|    |28  PC5 (AI 5)
//      (D 0) PD0  2|    |27  PC4 (AI 4)
//      (D 1) PD1  3|    |26  PC3 (AI 3)
//      (D 2) PD2  4|    |25  PC2 (AI 2)
// PWM+ (D 3) PD3  5|    |24  PC1 (AI 1)
//      (D 4) PD4  6|    |23  PC0 (AI 0)
//            VCC  7|    |22  GND
//            GND  8|    |21  AREF
//            PB6  9|    |20  AVCC
//            PB7 10|    |19  PB5 (D 13)
// PWM+ (D 5) PD5 11|    |18  PB4 (D 12)
// PWM+ (D 6) PD6 12|    |17  PB3 (D 11) PWM
//      (D 7) PD7 13|    |16  PB2 (D 10) PWM
//      (D 8) PB0 14|    |15  PB1 (D 9) PWM
//                  +----+
//
// (PWM+ indicates the additional PWM pins on the ATmega168.)

// ATMEL ATMEGA1280 / ARDUINO
//
// 0-7 PE0-PE7   works
// 8-13 PB0-PB5  works
// 14-21 PA0-PA7 works 
// 22-29 PH0-PH7 works
// 30-35 PG5-PG0 works
// 36-43 PC7-PC0 works
// 44-51 PJ7-PJ0 works
// 52-59 PL7-PL0 works
// 60-67 PD7-PD0 works
// A0-A7 PF0-PF7
// A8-A15 PK0-PK7


// these arrays map port names (e.g. port B) to the
// appropriate addresses for various functions (e.g. reading
// and writing)
const uint16_t PROGMEM port_to_mode_PGM[] = {
	NOT_A_PORT,
	NOT_A_PORT,
	(uint16_t) &DDRB,
	(uint16_t) &DDRC,
	(uint16_t) &DDRD,
};

const uint16_t PROGMEM port_to_output_PGM[] = {
	NOT_A_PORT,
	NOT_A_PORT,
	(uint16_t) &PORTB,
	(uint16_t) &PORTC,
	(uint16_t) &PORTD,
};

const uint16_t PROGMEM port_to_input_PGM[] = {
	NOT_A_PORT,
	NOT_A_PORT,
	(uint16_t) &PINB,
	(uint16_t) &PINC,
	(uint16_t) &PIND,
};

const uint8_t PROGMEM digital_pin_to_port_PGM[] = {
	PD, /* 0 */
	PD,
	PD,
	PD,
	PD,
	PD,
	PD,
	PD,
	PB, /* 8 */
	PB,
	PB,
	PB,
	PB,
	PB,
	PC, /* 14 */
	PC,
	PC,
	PC,
	PC,
	PC,
};

const uint8_t PROGMEM digital_pin_to_bit_mask_PGM[] = {
	_BV(0), /* 0, port D */
	_BV(1),
	_BV(2),
	_BV(3),
	_BV(4),
	_BV(5),
	_BV(6),
	_BV(7),
	_BV(0), /* 8, port B */
	_BV(1),
	_BV(2),
	_BV(3),
	_BV(4),
	_BV(5),
	_BV(0), /* 14, port C */
	_BV(1),
	_BV(2),
	_BV(3),
	_BV(4),
	_BV(5),
};

const uint8_t PROGMEM digital_pin_to_timer_PGM[] = {
	NOT_ON_TIMER, /* 0 - port D */
	NOT_ON_TIMER,
	NOT_ON_TIMER,
	// on the ATmega168, digital pin 3 has hardware pwm
#if defined(__AVR_ATmega8__)
	NOT_ON_TIMER,
#else
	TIMER2B,
#endif
	NOT_ON_TIMER,
	// on the ATmega168, digital pins 5 and 6 have hardware pwm
#if defined(__AVR_ATmega8__)
	NOT_ON_TIMER,
	NOT_ON_TIMER,
#else
	TIMER0B,
	TIMER0A,
#endif
	NOT_ON_TIMER,
	NOT_ON_TIMER, /* 8 - port B */
	TIMER1A,
	TIMER1B,
#if defined(__AVR_ATmega8__)
	TIMER2,
#else
	TIMER2A,
#endif
	NOT_ON_TIMER,
	NOT_ON_TIMER,
	NOT_ON_TIMER,
	NOT_ON_TIMER, /* 14 - port C */
	NOT_ON_TIMER,
	NOT_ON_TIMER,
	NOT_ON_TIMER,
	NOT_ON_TIMER,
};

#endif

// These serial port names are intended to allow libraries and architecture-neutral
// sketches to automatically default to the correct port name for a particular type
// of use.  For example, a GPS module would normally connect to SERIAL_PORT_HARDWARE_OPEN,
// the first hardware serial port whose RX/TX pins are not dedicated to another use.
//
// SERIAL_PORT_MONITOR        Port which normally prints to the Arduino Serial Monitor
//
// SERIAL_PORT_USBVIRTUAL     Port which is USB virtual serial
//
// SERIAL_PORT_LINUXBRIDGE    Port which connects to a Linux system via Bridge library
//
// SERIAL_PORT_HARDWARE       Hardware serial port, physical RX & TX pins.
//
// SERIAL_PORT_HARDWARE_OPEN  Hardware serial ports which are open for use.  Their RX & TX
//                            pins are NOT connected to anything by default.
#define SERIAL_PORT_MONITOR   Serial
#define SERIAL_PORT_HARDWARE  Serial

#endif
